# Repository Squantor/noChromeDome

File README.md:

# no chrome dome project
The no chrome dome, hence shortened to NCD from now one is a device that uses electrical pulses to reverse male pattern baldness. This project has been inspired by the paper ["Self-Activated Electrical Stimulation for Effective Hair Regeneration via a Wearable Omnidirectional Pulse Generator" by "Guang Yao, Dawei Jiang, Jun Li, Lei Kang, Sihong Chen, Yin Long, Yizhan Wang, Peng Huang, Yuan Lin, Weibo Cai and Xudong Wang"](papers/10.1021@acsnano.9b03912.pdf).
This paper describes a self powered device that uses electrical pulses to regrow hair in bald mice/rats. The researchers also used the device on his father and achieved good results. This motivated me to also try and make a device that might also achieve the same.
## Structure
This repository contains documentation, mechanical, hardware and software designs that I use in my experiments to recreate the paper. The structure of the repository is as follows:
* Papers: Contains papers that have relevant information
* Mechanical: Contains design files for mechanical components made in freecad
* [Electronics](electronics/README.md): Contains design files for electronic components, these are made with KiCad.
* Firmware: Contains source code for controlling the electronic components
* Software: Contains source code/scripts for measurement data from the NCD device
## Checking out
This project makes extensive use of submodules, use ```git clone --recurse-submodules https://github.com/Squantor/noChromeDome.git``` to clone the repository and its submodules in one go.

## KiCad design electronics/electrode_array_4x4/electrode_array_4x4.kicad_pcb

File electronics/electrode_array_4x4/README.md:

# 4 by 4 electrode array for nochromedome
Bigger array to cover a larger area, useful for the crown part of the head.
## TODO's
* schematic entry (Done)
* PCB layout (Done)
* Review with one night in between (Done)
* Produce at [OSHPARK](https://oshpark.com/) (WIP)
* Assemble
* Test & characterise
* update Readme.md with pictures and BOM

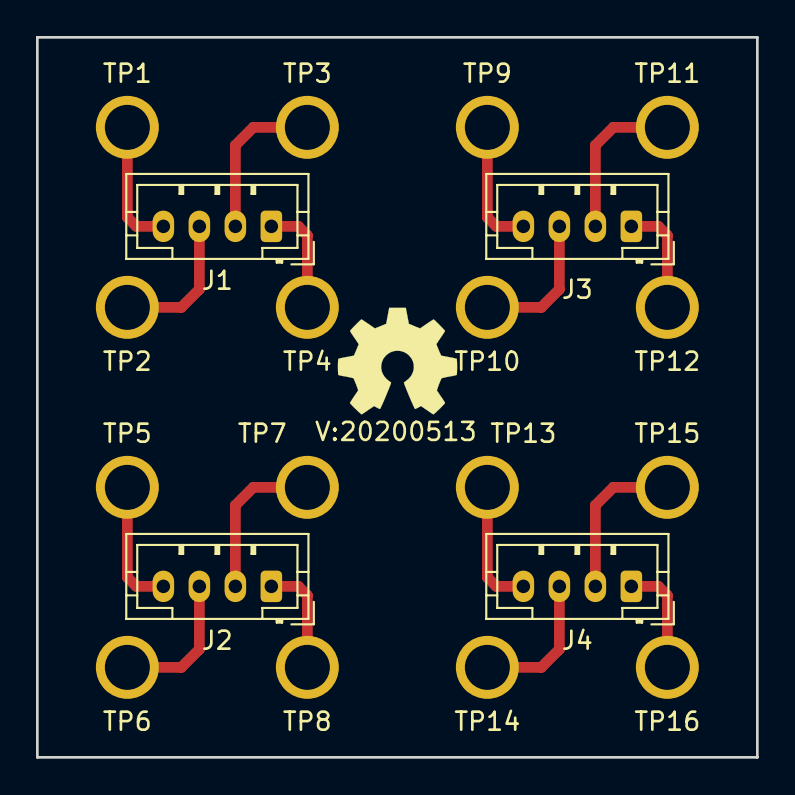
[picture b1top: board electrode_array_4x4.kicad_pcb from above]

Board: 2 copper layers, 40.0 x 40.0 mm, 22 parts (0 on the bottom side), 16 nets.

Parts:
J1, J2, J3, J4: Conn_01x04; JST_PH_B4B-PH-K_1x04_P2.00mm_Vertical
N1: OHWLOGO; OSHW-Symbol_6.7x6mm_SilkScreen
N2: 20200513; Label_version
TP1, TP2, TP3, TP4, TP5, TP6, TP7, TP8, TP9, TP10, TP11, TP12, TP13, TP14, TP15, TP16: testpad; hugepad_35X25hole

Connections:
/A1: J1.4, TP1.1
/A2: J1.2, TP3.1
/A3: J3.4, TP9.1
/A4: J3.2, TP11.1
/B1: J1.3, TP2.1
/B2: J1.1, TP4.1
/B3: J3.3, TP10.1
/B4: J3.1, TP12.1
/C1: J2.4, TP5.1
/C2: J2.2, TP7.1
/C3: J4.4, TP13.1
/C4: J4.2, TP15.1
/D1: J2.3, TP6.1
/D2: J2.1, TP8.1
/D3: J4.3, TP14.1
/D4: J4.1, TP16.1

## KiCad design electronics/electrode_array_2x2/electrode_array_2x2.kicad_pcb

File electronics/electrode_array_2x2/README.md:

# 2 by 2 electrode array, 1cm spacing
Simple electrode breakout with 1 cm spacing, 2 cm sized square PCB.
## TODO's
Still some things need to be done:
* schematic entry (Done)
* PCB layout (Done)
* Review with one night in between (Wip)
* Produce at [OSHPARK](https://oshpark.com/) (TODO)
* Assemble (TODO)
* Test & characterise (TODO)
* update Readme.md with pictures and BOM (TODO)
## BOM
## Pictures

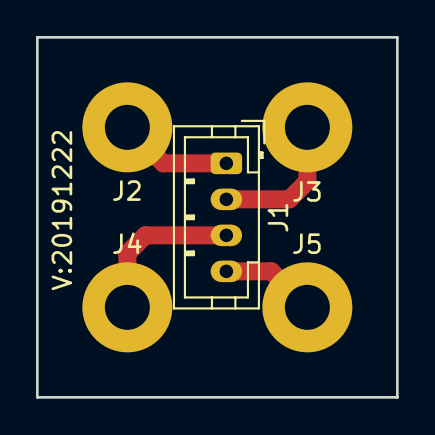
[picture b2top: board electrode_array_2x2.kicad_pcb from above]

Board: 2 copper layers, 20.0 x 20.0 mm, 6 parts (0 on the bottom side), 4 nets.

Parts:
J1: Conn_01x04; JST_PH_B4B-PH-K_1x04_P2.00mm_Vertical
J2: Electrode_A1; hugepad_50X25hole
J3: Electrode_B1; hugepad_50X25hole
J4: Electrode_A2; hugepad_50X25hole
J5: Electrode_B2; hugepad_50X25hole
N2: 20191222; Label_version

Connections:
/Electrode_A1: J1.1, J2.1
/Electrode_A2: J1.3, J4.1
/Electrode_B1: J1.2, J3.1
/Electrode_B2: J1.4, J5.1

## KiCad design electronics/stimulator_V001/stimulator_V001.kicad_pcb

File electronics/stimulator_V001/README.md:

# Prototype direct connection stimulator
This is a first tryout on a 16 electrode direct connected scalp stimulator.
## Principle of operation
Each electrode point is connected to one output of a 4 to 1 analog multiplexer. The input from the analog multiplexer is connected to a capacitor, value and type (film of ceramic) needs to be selected experimentally. The rest of the 4 to 1 multiplexer pins are connected as such
1. Electrode connection via a safety resistor of 10Kohm
2. No connection, this to keep the capacitor floating when needed
3. Programmable voltage source connection, connected to a voltage rail that can be controlled
4. ADC connection for measurements
## TODO's
Still some things need to be done:
* schematic entry (WIP)
* HSI (WIP
* PCB layout (TODO)
* Review with one night in between (TODO)
* Production (TODO)
* Assemble (TODO)
* Test & characterise (TODO)
## BOM
* 74HC4052 dual 1 to 4 analog multiplexers
## Pictures

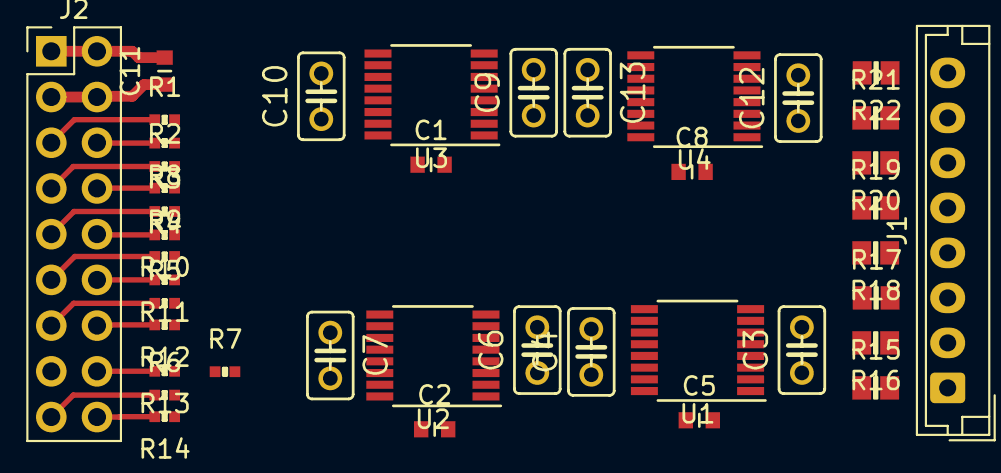
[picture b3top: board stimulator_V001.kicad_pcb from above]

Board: 2 copper layers, 43 parts (0 on the bottom side), 52 nets.

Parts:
C1, C2, C5, C8, C11: 10u; C_0603
C3, C4, C6, C7, C9, C10, C12, C13: 100n; C025-025X050
J1: Conn_01x08; JST_EH_B8B-EH-A_1x08_P2.50mm_Vertical
J2: Conn_02x08_Odd_Even; PinHeader_2x09_P2.54mm_Vertical
N1: OHWLOGO; OSHW-Symbol_6.7x6mm_SilkScreen
N2: 20191122; Label_version
R1, R2, R3, R4, R5, R6, R8, R9, R10, R11, R12, R13, R14: 100; R_0402_hand
R7: 4.7K; R_0402_hand
R15, R16, R17, R18, R19, R20, R21, R22: 10K; R_0805+0603
U1, U2, U3, U4: 74XX4052; TSSOP-16_4.4x5mm_P0.65mm

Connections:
/!Enable: R7.1, R13.1, U1.6, U2.6, U3.6, U4.6
/ADC0: R6.2, U1.5, U2.5, U3.5, U4.5
/ADC1: R14.1, U1.14, U2.14, U3.14, U4.14
/Electrode001: J1.1, R15.2
/Electrode002: J1.2, R16.1
/Electrode003: J1.3, R17.2
/Electrode004: J1.4, R18.1
/Electrode005: J1.5, R19.2
/Electrode006: J1.6, R20.1
/Electrode007: J1.7, R21.2
/Electrode008: J1.8, R22.1
/MUX000: R1.2, U1.10
/MUX001: R8.1, U1.9
/MUX002: R2.2, U2.10
/MUX003: R9.1, U2.9
/MUX004: R3.2, U3.10
/MUX005: R10.1, U3.9
/MUX006: R4.2, U4.10
/MUX007: R11.1, U4.9
/VDD: C1.1, C2.1, C5.1, C8.1, C11.1, J2.3, J2.4, R7.2, U1.16, U2.16, U3.16, U4.16
/VSS: C1.2, C2.2, C3.2, C4.2, C5.2, C6.2, C7.2, C8.2, C9.2, C10.2, C11.2, C12.2, C13.2, J2.1, J2.2, J2.15, U1.7, U1.8, U2.7, U2.8, U3.7, U3.8, U4.7, U4.8
/Vin_0: R5.2, U1.1, U2.1, U3.1, U4.1
/Vin_1: R12.1, U1.12, U2.12, U3.12, U4.12
/sheet5DDF521D/Electrode0_cap: C6.1, U2.3
/sheet5DDF521D/Electrode1_cap: C7.1, U2.13
/sheet5DE126B8/Electrode0_cap: C9.1, U3.3
/sheet5DE126B8/Electrode1_cap: C10.1, U3.13
/sheet5DE126DB/Electrode0_cap: C12.1, U4.3
/sheet5DE126DB/Electrode1_cap: C13.1, U4.13
/two electrode stimulator/Electrode0_cap: C3.1, U1.3
/two electrode stimulator/Electrode1_cap: C4.1, U1.13
unnamed: J2.5, R1.1
unnamed: J2.6, R8.2
unnamed: J2.7, R2.1
unnamed: J2.8, R9.2
unnamed: J2.9, R3.1
unnamed: J2.10, R10.2
unnamed: J2.11, R4.1
unnamed: J2.12, R11.2
unnamed: J2.13, R5.1
unnamed: J2.14, R12.2
unnamed: J2.16, R13.2
unnamed: J2.17, R6.1
unnamed: J2.18, R14.2
unnamed: R15.1, U1.4
unnamed: R16.2, U1.11
unnamed: R17.1, U2.4
unnamed: R18.2, U2.11
unnamed: R19.1, U3.4
unnamed: R20.2, U3.11
unnamed: R21.1, U4.4
unnamed: R22.2, U4.11

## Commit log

2019-11-08 added initial readme
2019-11-08 added paper that inspired this project
2019-11-08 added PCB library
2019-11-08 fixed reponame in landing README.md
2019-11-08 moving some directories around
2019-11-08 added gitignore for kicad and first stimulator prototype
2019-11-08 added 4 way capacitive switch
2019-11-08 further connections in subschematic
2019-11-08 updated pcb library
2019-11-08 added mux
2019-11-22 started with a simple single mux 2 channel stimulator
2019-11-22 finished 2 channel stimulator
2019-11-22 added a bunch more muxes, fails DRC
2019-11-22 updated bugfix in PCB library
2019-11-22 started PCB layout, DRC passes
2019-11-22 reduced digital resistors to 0402
2019-11-22 further placement
2019-11-22 more placement iterations
2019-11-22 more placement optimizations
2019-12-22 added electrode array pcb
2019-12-22 WIP PCB layout
2019-12-23 changed connector, silk placement
2019-12-23 updated readme status
2020-04-19 updated PCB component library
2020-04-19 updated electrode array pcb to larger hole sizes
2020-05-13 started with 4 by 4 electrode array
2020-05-13 completed 4by4 electrode array
2020-05-14 updated progress
2020-06-05 added libMcuLL
2020-06-05 added new ignores, added initial software project
2020-06-19 removed log files
2020-06-19 fixed up some paths
2020-06-19 added board definitions for first prototype board
2020-06-19 added new board definition to build
2020-06-19 updated a define to find symbols in VScode
2020-06-19 added crystal oscillator initialisation
2020-06-19 newer libmcull
2020-06-19 verify clock output speed
2020-06-19 getting debugging operational
2020-06-19 added clock default default configuration
2020-06-19 added clock initialisation and verification
2020-06-19 removed old clockout verification code
2020-06-19 WIP UART, but seems to use a lot of flash due to division routines, need to patch this
2020-06-19 integrated romdiv usage into LPC824 template, time to move to libmcull examples
2020-06-19 fixed error with using division routines
2020-06-19 added a bunch of files to help with uart output
2020-06-19 functional debugging UART output
2020-07-17 updated to newer libMcuLL
2020-07-17 debugging problem with initializing a commandline prompt
2020-07-17 added cortex-debug config
2020-07-17 switched to newer build environment
2020-07-17 fixed crash with return handling, better pay attention to warnings
2020-07-17 added eclipse ignores
